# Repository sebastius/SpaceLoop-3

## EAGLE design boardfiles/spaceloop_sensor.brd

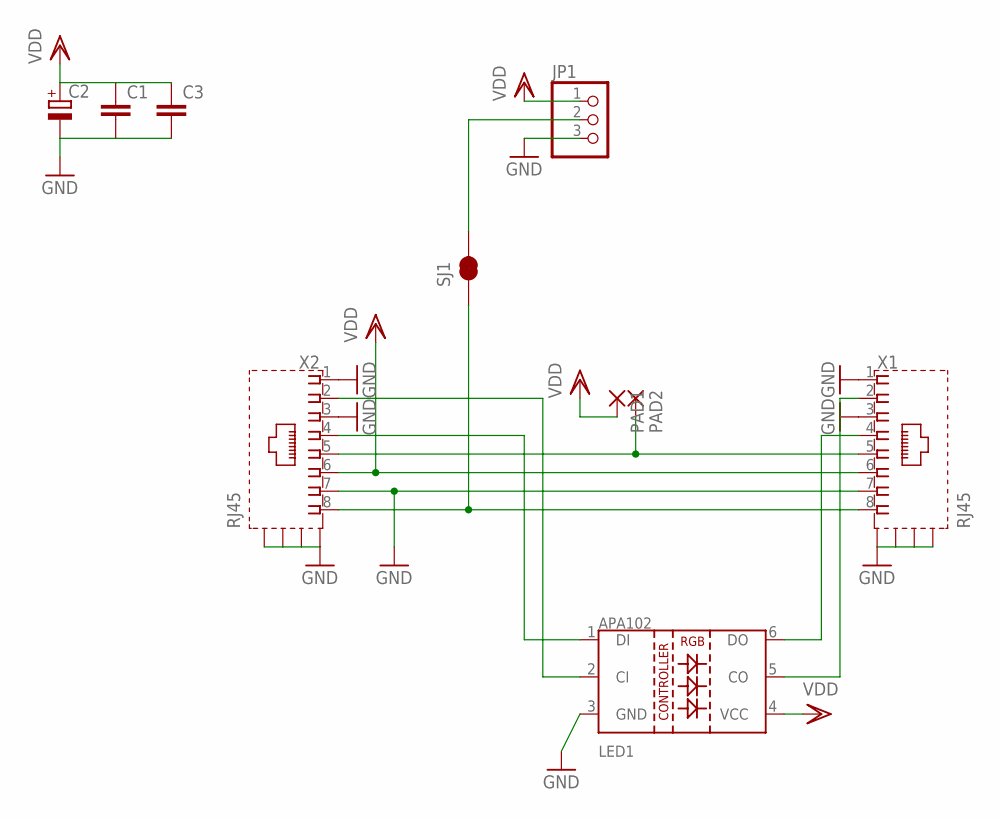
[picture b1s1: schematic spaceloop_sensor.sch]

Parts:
C1, C3: C-EUC0805K; C0805K
C2: CPOL-EU150CLZ-0810; 150CLZ-0810
JP1: PINHD-1X3; 1X03
LED1: LED-APA102
PAD1, PAD2: SMD5; SMD2,54-5,08
SJ1: JUMPER-PAD-2-NC_BY_TRACENO_SILK; PAD-JUMPER-2-NC_BY_TRACE_NO_SILK
X1, X2: RJ45; RJ45-SHIELD2

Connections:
GND: C1.2, C2.-, C3.2, JP1.3, LED1.3 (GND), X1.1, X1.3, X1.7, X1.S1 (S), X1.S2 (S), X1.S3 (S), X1.S4 (S), X2.1, X2.3, X2.7, X2.S1 (S), X2.S2 (S), X2.S3 (S), X2.S4 (S)
unnamed: LED1.6 (DO), X1.4
unnamed: SJ1.1, X1.8, X2.8
unnamed: LED1.5 (CO), X1.2
unnamed: LED1.2 (CI), X2.2
unnamed: LED1.1 (DI), X2.4
unnamed: PAD2.1, X1.5, X2.5
unnamed: JP1.2, SJ1.2
VDD: C1.1, C2.+, C3.1, JP1.1, LED1.4 (VCC), PAD1.1, X1.6, X2.6

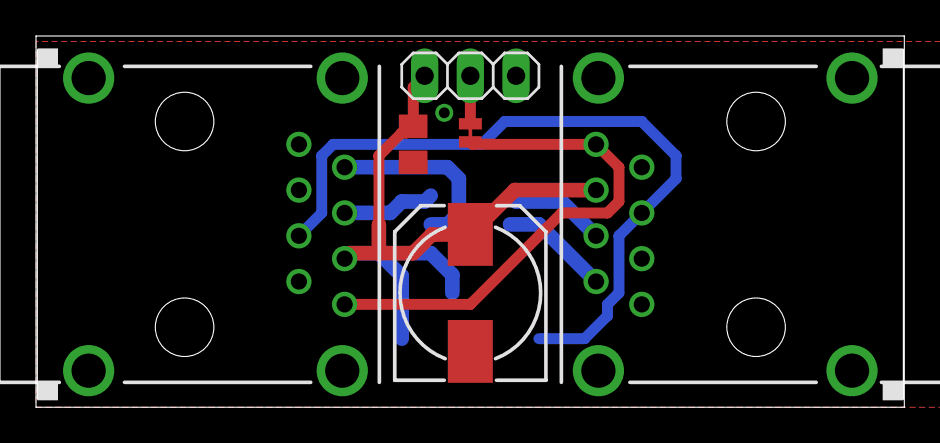
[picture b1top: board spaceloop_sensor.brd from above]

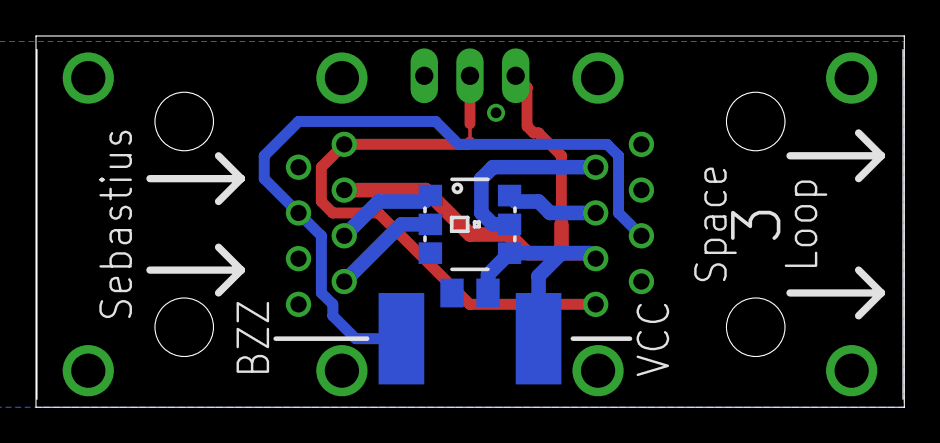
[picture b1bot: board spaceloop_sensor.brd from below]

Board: 2 copper layers, 48.2 x 20.6 mm, 10 parts (4 on the bottom side), 9 nets.

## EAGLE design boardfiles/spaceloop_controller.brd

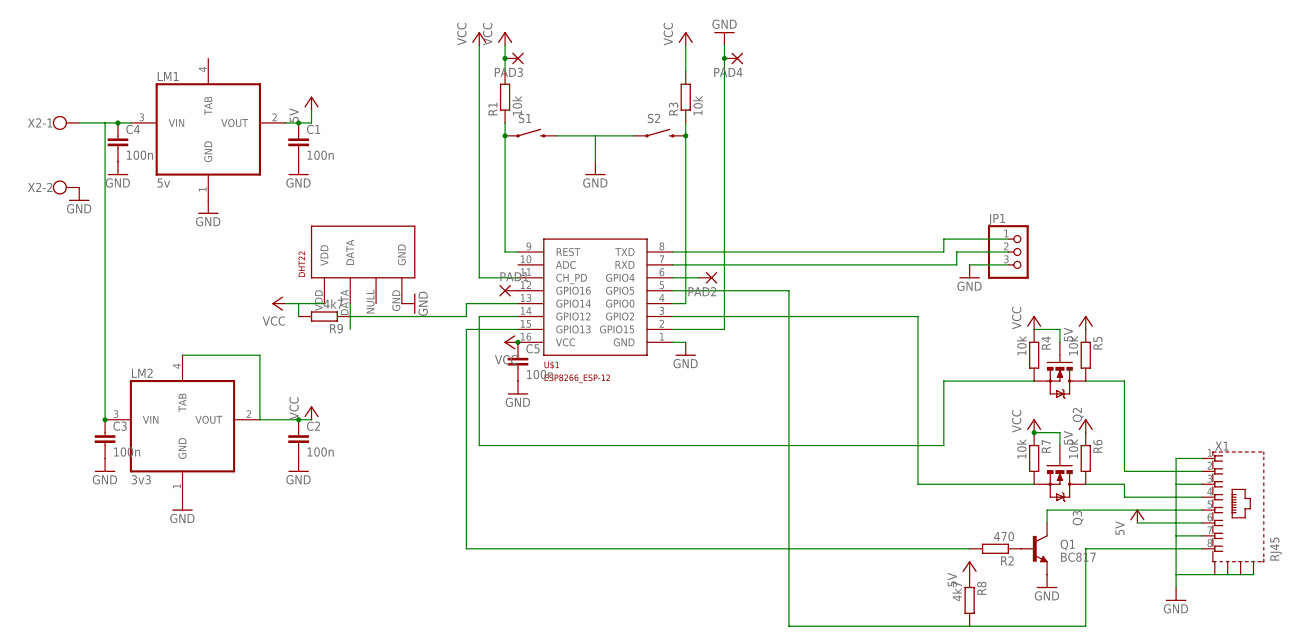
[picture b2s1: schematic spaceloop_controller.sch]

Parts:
C1, C2, C3, C4, C5: 100n; C0805
DHT22: RHT03_DHT-22_AM2302WIRED; AM2302
JP1: PINHD-1X3; 1X03
LM1: 5v; SOT223
LM2: 3v3; SOT223
PAD1, PAD2, PAD3, PAD4: SMD2; SMD1,27-2,54
Q1: BC817; SOT23-3
Q2, Q3: BSS138; SOT23-3
R1, R3, R4, R5, R6, R7: 10k; R0805
R2: 470; R0805
R8, R9: 4k7; R0805
S1, S2: SWITCH-MOMENTARY-2SMD-1101NE; TACTILE-SWITCH-1101NE
U$1: ESP8266_ESP-12; ESP8266-ESP12
X1: RJ45; RJ45-SHIELD2
X2: W237-102

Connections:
+5V: C1.1, LM1.2 (VOUT), R5.1, R6.1, R8.1, X1.6
GND: C1.2, C2.2, C3.2, C4.2, C5.2, DHT22.GND, JP1.3, LM1.1 (GND), LM2.1 (GND), PAD4.1, Q1.2 (E), S1.2, S2.1, U$1.1 (GND), U$1.2 (GPIO15), X1.1, X1.3, X1.7, X1.S1 (S), X1.S2 (S), X1.S3 (S), X1.S4 (S), X2.2
unnamed: Q1.1 (B), R2.1
unnamed: Q1.3 (C), X1.5
unnamed: JP1.1, U$1.8 (TXD)
unnamed: JP1.2, U$1.7 (RXD)
unnamed: R1.1, S1.1, U$1.9 (REST)
unnamed: R3.1, S2.2, U$1.4 (GPIO0)
unnamed: PAD1.1, U$1.12 (GPIO16)
unnamed: Q2.2 (S), R4.2, U$1.14 (GPIO12)
unnamed: Q3.2 (S), R7.2, U$1.3 (GPIO2)
unnamed: Q3.3 (D), R6.2, X1.4
unnamed: R8.2, U$1.5 (GPIO5), X1.8
unnamed: PAD2.1, U$1.6 (GPIO4)
unnamed: R2.2, U$1.15 (GPIO13)
unnamed: DHT22.DATA, R9.1, U$1.13 (GPIO14)
unnamed: C3.1, C4.1, LM1.3 (VIN), LM2.3 (VIN), X2.1
unnamed: Q2.3 (D), R5.2, X1.2
VCC: C2.1, C5.1, DHT22.VDD, LM2.2 (VOUT), LM2.4 (TAB), PAD3.1, Q2.1 (G), Q3.1 (G), R1.2, R3.2, R4.1, R7.1, R9.2, U$1.11 (CH_PD), U$1.16 (VCC)

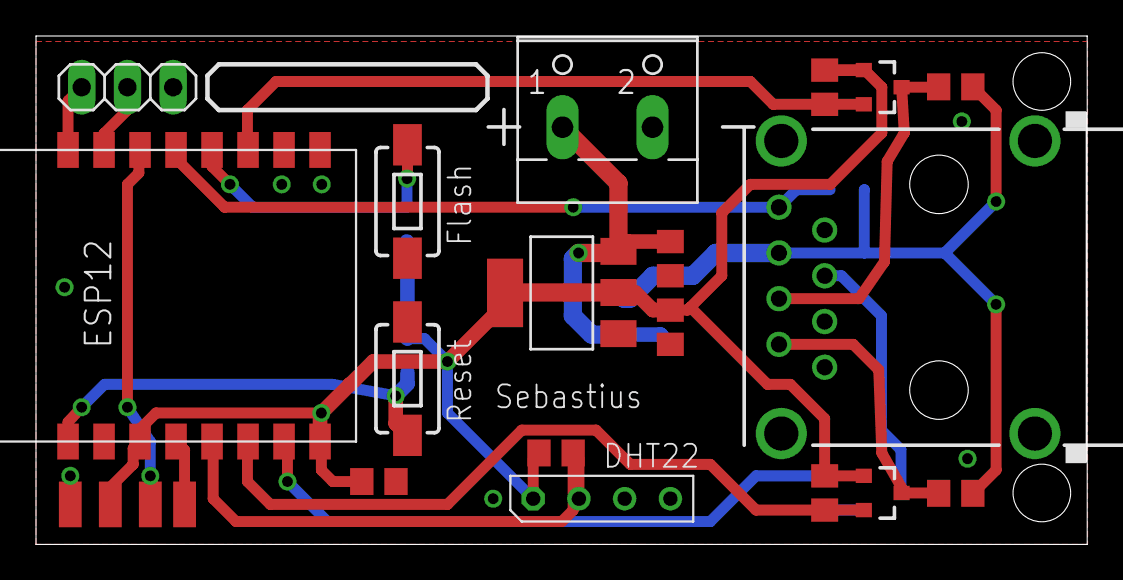
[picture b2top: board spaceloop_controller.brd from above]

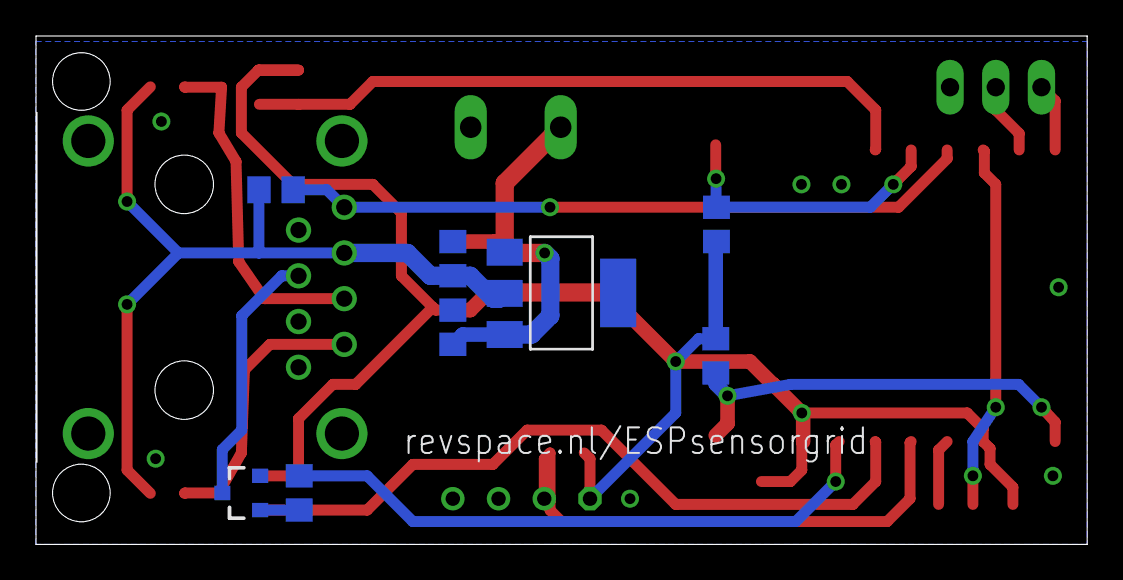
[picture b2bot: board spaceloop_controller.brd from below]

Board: 2 copper layers, 58.4 x 28.2 mm, 30 parts (8 on the bottom side), 19 nets.

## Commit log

2016-09-17 First Code
    mostly working, nomz and doorbell are breaking code, so the MQTT stream
    ques behind it. If there are multiple nomz/doorbells pressed that will
    cause issues.
2016-09-19 Better NOMZ/DOORBELL handling
    Als het goed is zet hij nu niet meerdere nomz in de wachtrij. Wat hij
    wel mogelijk doet is een nomz opnieuw instarten, dus dan kan een nomz
    bv 32 seconden duren. Dat zal ik moeten testen…
2016-09-19 Boards erbij
    Whoppa
2016-09-19 Betere gitignore

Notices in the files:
parts and their libraries:
SparkFun-Electromechanical: Licensing: Creative Commons ShareAlike 4.0 International - https://creativecommons.org/licenses/by-sa/4.0
